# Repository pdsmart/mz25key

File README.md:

# mz25key
A PS/2 to Sharp MZ-2500/MZ-2800 Interface

The mz25key now uses the SharKey firmware. If the build configuration (menuconfig -> SharpKey Configuration -> Build target -> mz25key
is set to an MZ2500 or MZ2800 then no changes are needed to hardware, just upload the firmware via the programmer port and once uploaded
future updates can be made via OTA. 

A modification can be made to an mz25key to allow it to run SharpKey firmware without specific build target. This can be achieved with a
100R resistor placed between pin14 (GPIO12) of the ESP32 and pin 8 of the host interface header J1. The advantage of this modification is it makes
the mz25key compatible with the SharpKey and if you used a 9pin header on the host interface, you can swap cables around to target different 
hosts.

Please see my website, https://eaw.app for more documentation and recent updates. 

The source code for the mz25key is identical to the SharpKey, just the build time configuration via the KConfig menu. The provided sdkconfig
is setup so that the source code will build the mz25key.

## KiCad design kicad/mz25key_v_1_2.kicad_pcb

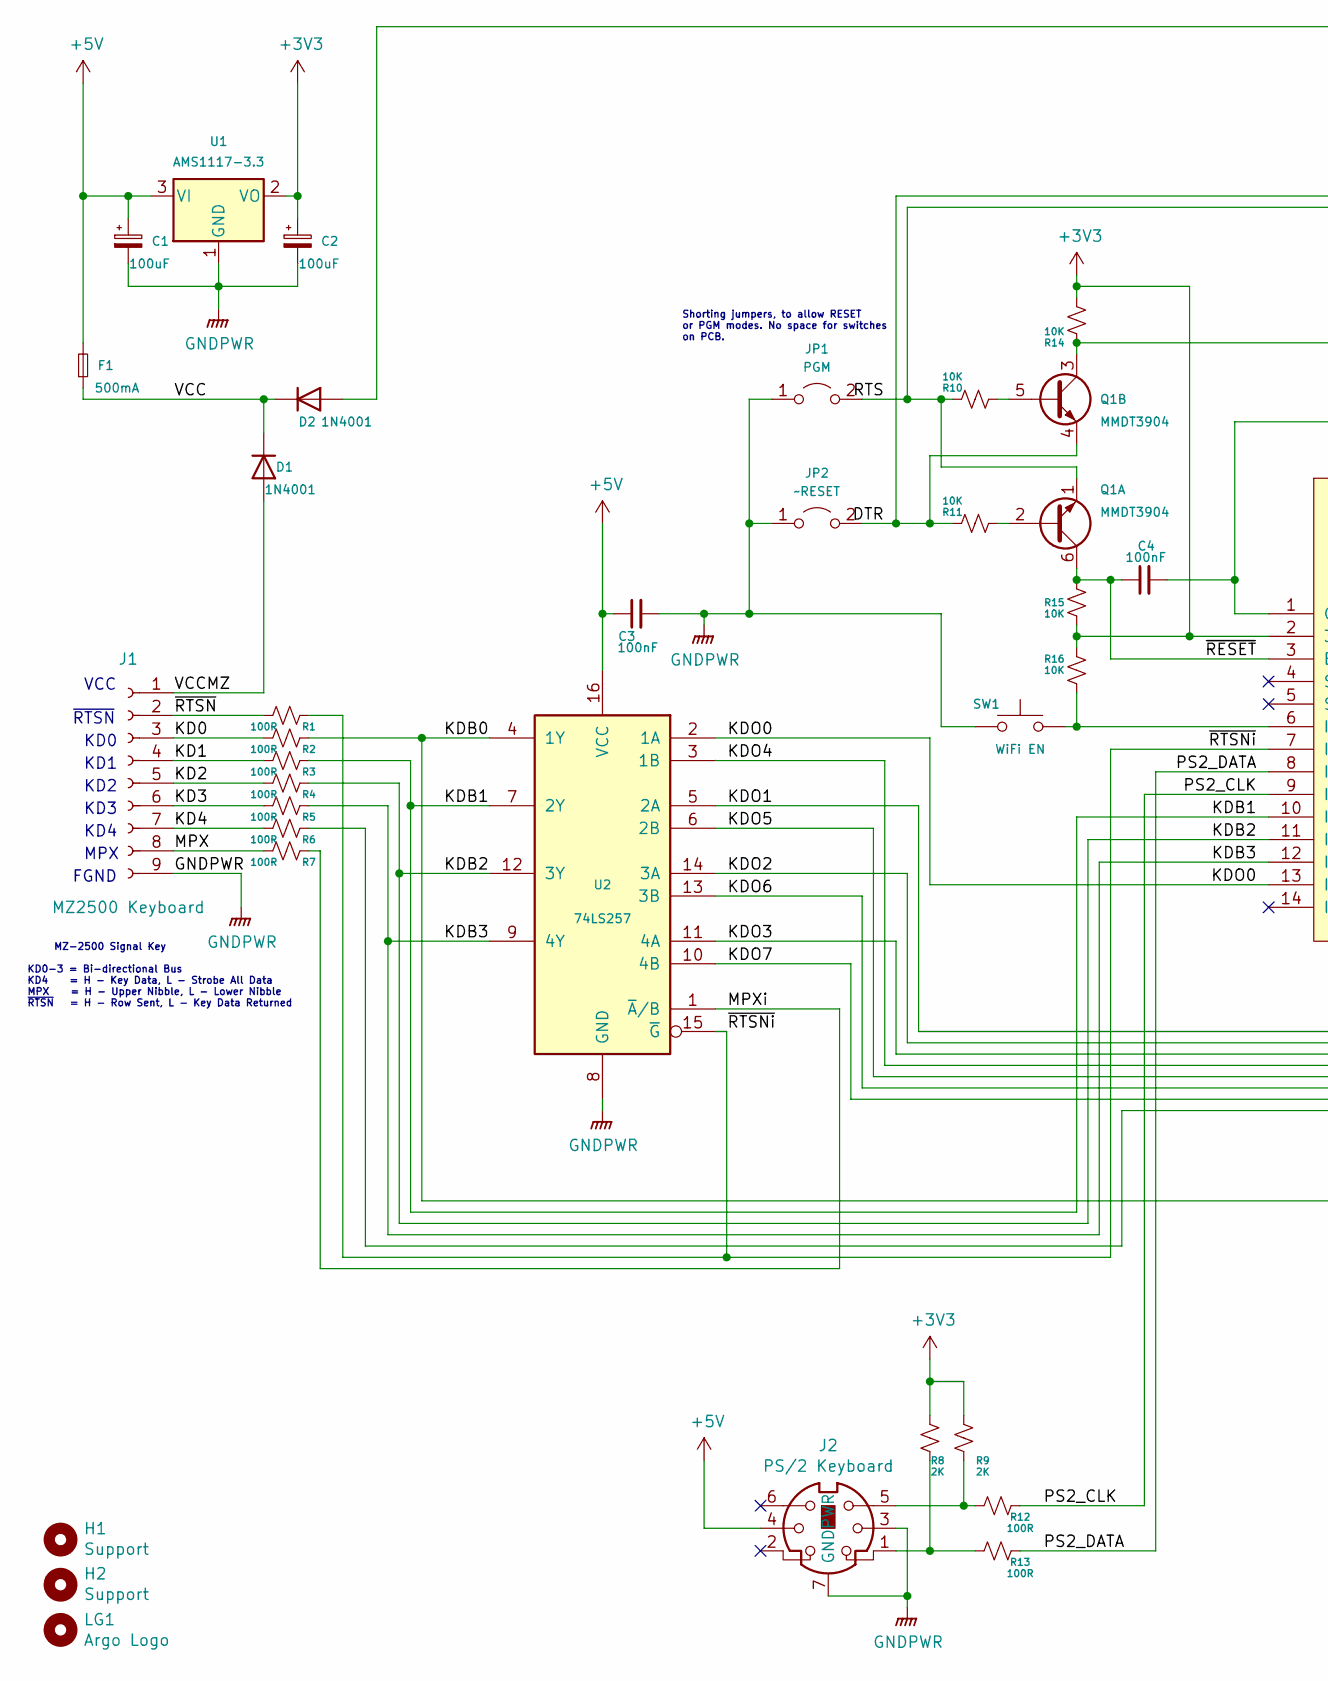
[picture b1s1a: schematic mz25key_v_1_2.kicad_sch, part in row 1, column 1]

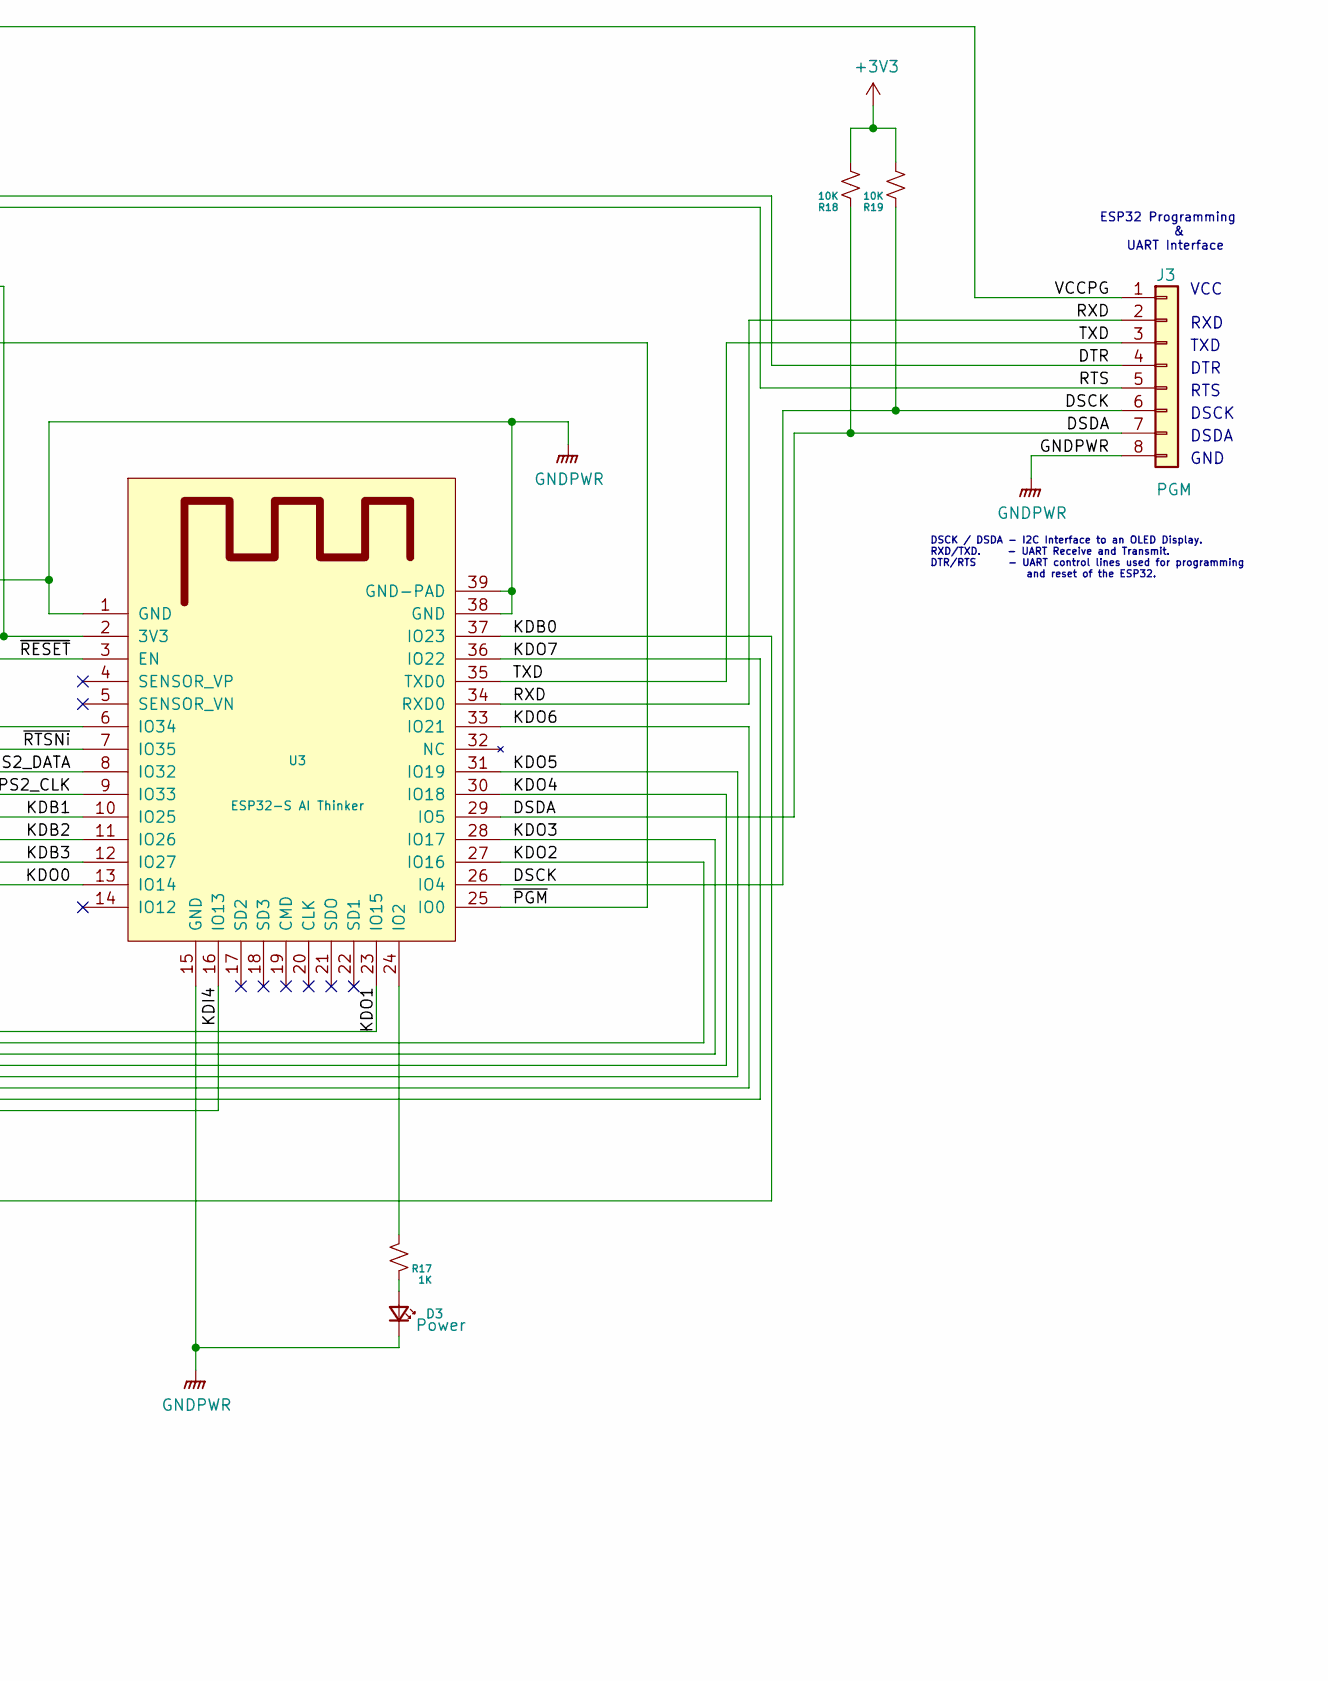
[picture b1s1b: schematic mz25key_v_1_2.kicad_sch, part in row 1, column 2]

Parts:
C1, C2: 100uF; C_1210_3225Metric_Pad1.42x2.65mm_HandSolder
C3, C4: 100nF; C_0805_2012Metric
D1, D2: 1N4001; D_1206_3216Metric
D3: Power; LED_D3.0mm_Clear
F1: 500mA; Fuse_1806_4516Metric
H1, H2: Support; MountingHole_2.1mm
J1: MZ2500 Keyboard; PinHeader_1x09_P2.00mm_Vertical
J2: PS/2 Keyboard; Mini_din6_ps2
J3: PGM; PinHeader_1x08_P2.00mm_Vertical
JP1: PGM; PinHeader_1x02_P1.27mm_Vertical
JP2: ~RESET; PinHeader_1x02_P1.27mm_Vertical
LG1: Argo Logo; Argo
Q1: MMDT3904; SOT-363_SC-70-6
R1, R2, R3, R4, R5, R6, R7, R12, R13: 100R; R_0805_2012Metric
R8, R9: 2K; R_0805_2012Metric
R10, R11, R14, R15, R16, R18, R19: 10K; R_0805_2012Metric
R17: 1K; R_0805_2012Metric
SW1: WiFi EN; SW_SPST_B3S-1000
U1: AMS1117-3.3; SOT-223-3_TabPin2
U2: 74LS257; SOIC-16_3.9x9.9mm_P1.27mm
U3: ESP32-S AI Thinker; ESP32-S

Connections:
+3V3: C2.1, R8.1, R9.1, R14.2, R15.1, R16.2, R18.2, R19.2, U1.2 (VO), U3.2 (3V3)
+5V: C1.1, C3.1, F1.2, J2.4, U1.3 (VI), U2.16 (VCC)
/DSCK: J3.6, R19.1, U3.26 (IO4)
/DSDA: J3.7, R18.1, U3.29 (IO5)
/DTR: J3.4, JP2.2 (B), Q1.4 (E2), R11.2
/KD0: J1.3, R2.1
/KD1: J1.4, R3.1
/KD2: J1.5, R4.1
/KD3: J1.6, R5.1
/KD4: J1.7, R6.1
/KDB0: R2.2, U2.4 (1Y), U3.37 (IO23)
/KDB1: R3.2, U2.7 (2Y), U3.10 (IO25)
/KDB2: R4.2, U2.12 (3Y), U3.11 (IO26)
/KDB3: R5.2, U2.9 (4Y), U3.12 (IO27)
/KDI4: R6.2, U3.16 (IO13)
/KDO0: U2.2 (1A), U3.13 (IO14)
/KDO1: U2.5 (2A), U3.23 (IO15)
/KDO2: U2.14 (3A), U3.27 (IO16)
/KDO3: U2.11 (4A), U3.28 (IO17)
/KDO4: U2.3 (1B), U3.30 (IO18)
/KDO5: U2.6 (2B), U3.31 (IO19)
/KDO6: U2.13 (3B), U3.33 (IO21)
/KDO7: U2.10 (4B), U3.36 (IO22)
/MPX: J1.8, R7.1
/MPXi: R7.2, U2.1 (~A/B)
/PS2_CLK: R12.2, U3.9 (IO33)
/PS2_DATA: R13.2, U3.8 (IO32)
/RTS: J3.5, JP1.2 (B), Q1.1 (E1), R10.2
/RXD: J3.2, U3.34 (RXD0)
/TXD: J3.3, U3.35 (TXD0)
/VCC: D1.1 (K), D2.1 (K), F1.1
/VCCMZ: D1.2 (A), J1.1
/VCCPG: D2.2 (A), J3.1
/~PGM: Q1.3 (C2), R14.1, U3.25 (IO0)
/~RESET: C4.1, Q1.6 (C1), R15.2, U3.3 (EN)
/~RTSNi: R1.2, U2.15 (~G), U3.7 (IO35)
/~RTSN: J1.2, R1.1
GNDPWR: C1.2, C2.2, C3.2, C4.2, D3.1 (K), J1.9, J2.3, J2.7 (GNDPWR), J2.GND, J3.8, JP1.1 (A), JP2.1 (A), SW1.1, U1.1 (GND), U2.8 (GND), U3.1 (GND), U3.15 (GND), U3.38 (GND), U3.39 (GND-PAD)
unnamed: D3.2 (A), R17.2
unnamed: J2.1, R8.2, R13.1
unnamed: J2.5, R9.2, R12.1
unnamed: Q1.2 (B1), R11.1
unnamed: Q1.5 (B2), R10.1
unnamed: R16.1, SW1.2, U3.6 (IO34)
unnamed: R17.1, U3.24 (IO2)

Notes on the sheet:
KD3
Shorting jumpers, to allow RESET or PGM modes. No space for switches on PCB.
~{RTSN}
MPX
DSCK
DTR
RTS
KD2
TXD
VCC
ESP32 Programming & UART Interface
RXD
DSCK / DSDA - I2C Interface to an OLED Display. RXD/TXD. - UART Receive and Transmit. DTR/RTS - UART control lines used for programming and reset of the ESP32.
KD0
KD4
FGND
KD1
MZ-2500 Signal Key KD0-3 = Bi-directional Bus KD4 = H - Key Data, L - Strobe All Data MPX = H - Upper Nibble, L - Lower Nibble ~{RTSN} = H - Row Sent, L - Key Data Returned
DSDA
GND

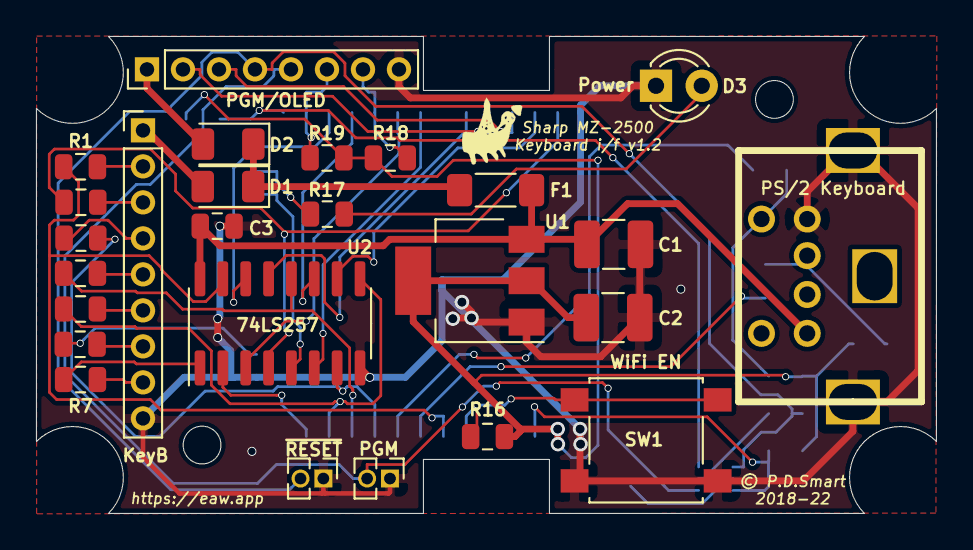
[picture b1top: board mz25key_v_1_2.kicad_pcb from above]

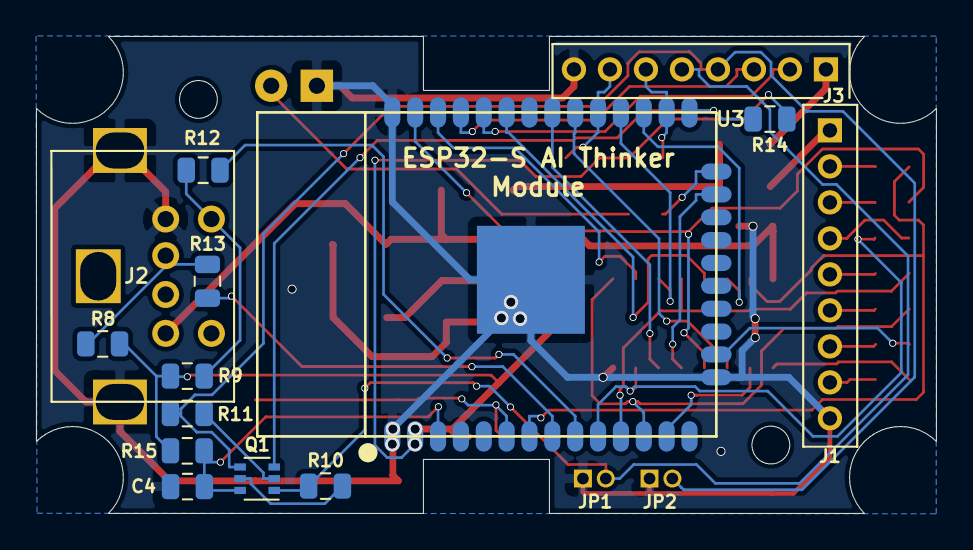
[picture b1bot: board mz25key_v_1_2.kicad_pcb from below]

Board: 2 copper layers, 50.0 x 26.5 mm, 40 parts (11 on the bottom side), 45 nets.

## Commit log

2022-01-29 Initial push
2022-01-29 Updates with the mzInterface stage
2022-01-30 Updates to mapping table for Wyse KB3926
2022-01-30 Comment changes
2022-01-30 Started collecting useful docs
2022-02-13 First code release
2022-02-13 Updated ignore list
2022-03-10 Added PCB and Schematic files
2022-03-10 Typo
2022-03-12 added git attributes
2022-06-02 Updated to SharpKey firmware
2022-06-19 Updating with latest sharpkey build.
2022-06-25 Updates and compile and test verification
2022-09-04 Updated with source code
2022-09-04 Updated license file

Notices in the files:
kicad/mz25key_v_1_2.kicad_pcb:
© P.D.Smart
